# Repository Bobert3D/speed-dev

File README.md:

An ultra fast speed run made Dev board!

Oki so this is a Speedrun dev board so the readme is also going to be Speedrun!
I started with the not so hard schematic!  Schematic!!!

I then continued to the PCB and the layout part so I know where I want things (roughly lol) once I finished that I started to route from the RP2040 outward and then realized that if I wanted this to be ultra compact and cute I needed 4 layers soooo. I did that lol and I continued to do it and then I'm here writing this readme and about to do BOM! Thanks!  PCB Photo!!! 
 3D Render!
If you want to see the CAD/3D design take a peek here!! https://cad.onshape.com/documents/b9c1c579f6d2acbbd7cd123c/w/911443ecb6c1df3a912c9fca/e/5be0e992ba93a5b27c93457b?renderMode=0&uiState=6ac969cc2a2592bfad12f0f4

 BOM!

#BOM!
| Id | Designator                              | Footprint                           | Quantity | Designation                 | Supplier and ref |   |   |
|----|-----------------------------------------|-------------------------------------|----------|-----------------------------|------------------|---|---|
| 1  | SW1                                     | SW_Push_SPST_NO_Alps_SKRK           | 1        | SW_Push                     |                  |   |   |
| 2  | C8,C17                                  | C_0402_1005Metric                   | 2        | 1uF                         |                  |   |   |
| 3  | C11,C15,C7,C16,C13,C12,C9,C10,C5,C14,C6 | C_0402_1005Metric                   | 11       | 0.1uF                       |                  |   |   |
| 4  | Y1                                      | Crystal_SMD_3225-4Pin_3.2x2.5mm     | 1        | 12 MHz                      |                  |   |   |
| 5  | U4                                      | SOT-23                              | 1        | MCP1700x-330xxTT            |                  |   |   |
| 6  | R2,R5,R1,R6                             | R_0402_1005Metric                   | 4        | 5.1K                        |                  |   |   |
| 7  | J3                                      | PinHeader_1x03_P2.54mm_Vertical     | 1        | Conn_01x03                  |                  |   |   |
| 8  | R4                                      | R_0402_1005Metric                   | 1        | 10K                         |                  |   |   |
| 9  | U3                                      | QFN-56-1EP_7x7mm_P0.4mm_EP3.2x3.2mm | 1        | RP2040                      |                  |   |   |
| 10 | C2,C1                                   | C_0201_0603Metric                   | 2        | 10uF                        |                  |   |   |
| 11 | J2,J4                                   | PinHeader_1x20_P2.54mm_Vertical     | 2        | Conn_01x20                  |                  |   |   |
| 12 | R3                                      | R_0402_1005Metric                   | 1        | 1K                          |                  |   |   |
| 13 | U2                                      | SOIC-8_5.3x5.3mm_P1.27mm            | 1        | W25Q128JVS                  |                  |   |   |
| 14 | J1                                      | USB_C_Receptacle_HRO_TYPE-C-31-M-12 | 1        | USB_C_Receptacle_USB2.0_14P |                  |   |   |
| 15 | C4,C3                                   | C_0603_1608Metric                   | 2        | 15pF                        |                  |   |   |

## FAQ

#### BOM?

There are 2 BOM technically one has the LCSC part numbers and the others is a quote from LCSC with links to parts too!

#### Is this good for beginners?

Yes!!! ITS THE BENCHY PCB EQUIVALENT!!

#### How many layers is the PCB?

This is a 4 layer PCB!

#### Can I contribute?

YES YOU CAN!!!! Take a peek at the Contributing section for a better guide on contributing!

## Authors

- [@bobert3d](https://www.github.com/Bobert3D)

- [@vms-hc](https://www.github.com/VMS-HC)

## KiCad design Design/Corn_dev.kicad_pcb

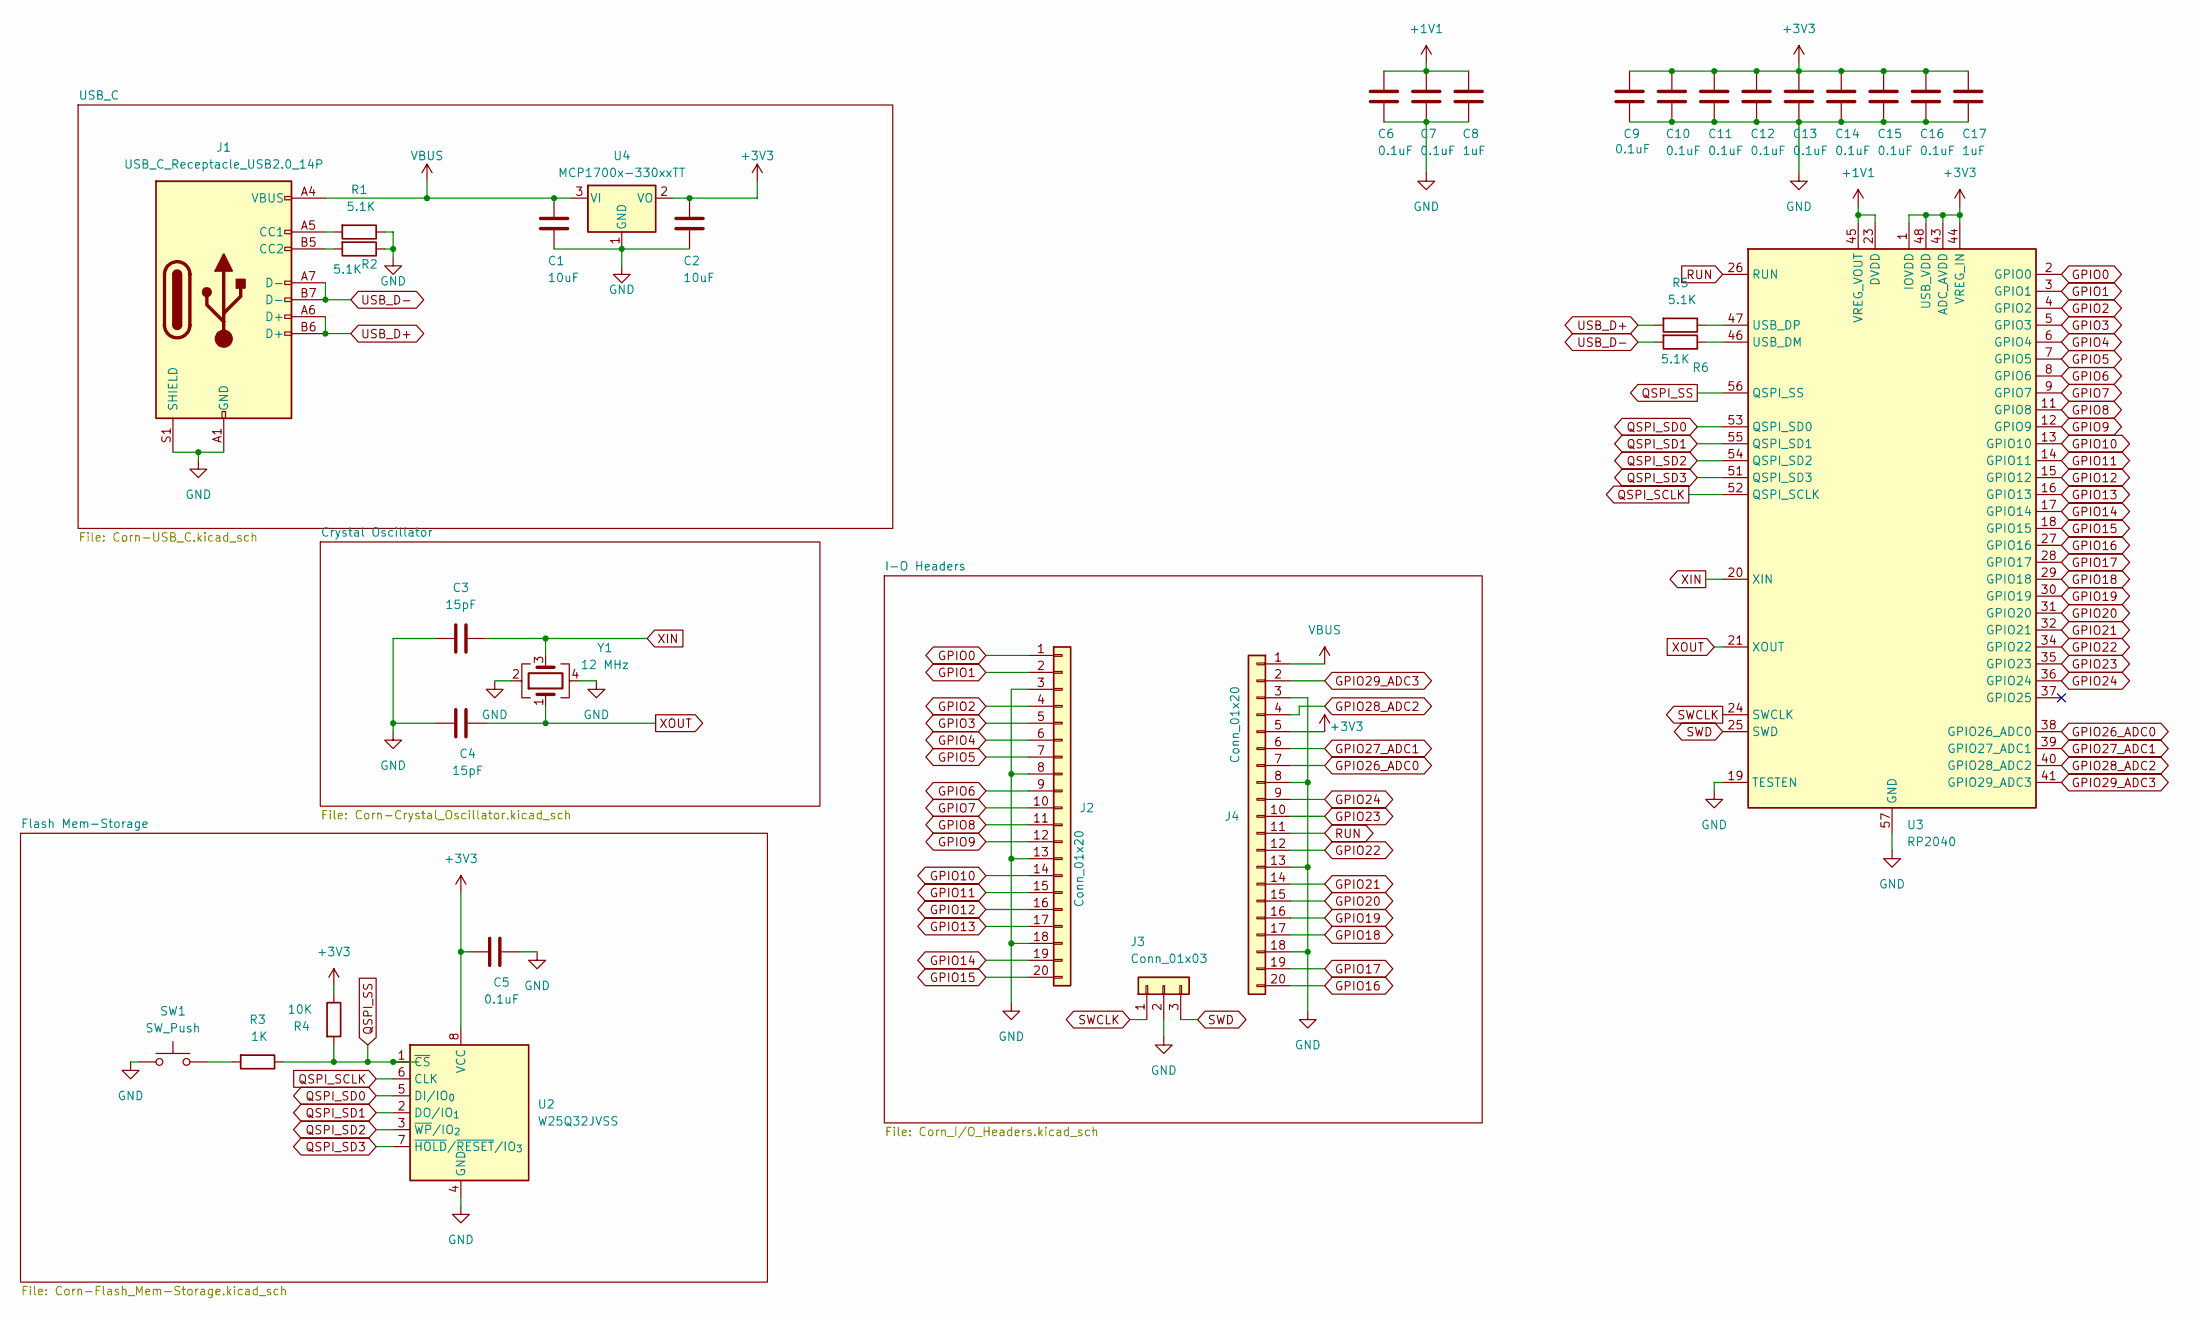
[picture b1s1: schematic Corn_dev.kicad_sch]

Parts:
C1, C2: 10uF; C_0201_0603Metric
C3, C4: 15pF; C_0603_1608Metric
C5, C6, C7, C9, C10, C11, C12, C13, C14, C15, C16: 0.1uF; C_0402_1005Metric
C8, C17: 1uF; C_0402_1005Metric
J1: USB_C_Receptacle_USB2.0_14P; USB_C_Receptacle_HRO_TYPE-C-31-M-12
J2, J4: Conn_01x20; PinHeader_1x20_P2.54mm_Vertical
J3: Conn_01x03; PinHeader_1x03_P2.54mm_Vertical
R1, R2, R5, R6: 5.1K; R_0402_1005Metric
R3: 1K; R_0402_1005Metric
R4: 10K; R_0402_1005Metric
SW1: SW_Push; SW_Push_SPST_NO_Alps_SKRK
U2: W25Q32JVSS; SOIC-8_5.3x5.3mm_P1.27mm
U3: RP2040; QFN-56-1EP_7x7mm_P0.4mm_EP3.2x3.2mm
U4: MCP1700x-330xxTT; SOT-23
Y1: 12 MHz; Crystal_SMD_3225-4Pin_3.2x2.5mm

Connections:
+1V1: C6.1, C7.1, C8.1, U3.23 (DVDD), U3.45 (VREG_VOUT), U3.50 (DVDD)
+3V3: C2.1, C5.1, C9.1, C10.1, C11.1, C12.1, C13.1, C14.1, C15.1, C16.1, C17.1, J4.5, R4.1, U2.8 (VCC), U3.1 (IOVDD), U3.10 (IOVDD), U3.22 (IOVDD), U3.33 (IOVDD), U3.42 (IOVDD), U3.43 (ADC_AVDD), U3.44 (VREG_IN), U3.48 (USB_VDD), U3.49 (IOVDD), U4.2 (VO)
GND: C1.2, C2.2, C3.1, C4.1, C5.2, C6.2, C7.2, C8.2, C9.2, C10.2, C11.2, C12.2, C13.2, C14.2, C15.2, C16.2, C17.2, J1.A1 (GND), J1.A12 (GND), J1.B1 (GND), J1.B12 (GND), J1.S1 (SHIELD), J2.3, J2.8, J2.13, J2.18, J3.2, J4.3, J4.8, J4.13, J4.18, R1.1, R2.1, SW1.1, U2.4 (GND), U3.19 (TESTEN), U3.57 (GND), U4.1 (GND), Y1.2, Y1.4
GPIO0: J2.1, U3.2 (GPIO0)
GPIO1: J2.2, U3.3 (GPIO1)
GPIO2: J2.4, U3.4 (GPIO2)
GPIO3: J2.5, U3.5 (GPIO3)
GPIO4: J2.6, U3.6 (GPIO4)
GPIO5: J2.7, U3.7 (GPIO5)
GPIO6: J2.9, U3.8 (GPIO6)
GPIO7: J2.10, U3.9 (GPIO7)
GPIO8: J2.11, U3.11 (GPIO8)
GPIO9: J2.12, U3.12 (GPIO9)
GPIO10: J2.14, U3.13 (GPIO10)
GPIO11: J2.15, U3.14 (GPIO11)
GPIO12: J2.16, U3.15 (GPIO12)
GPIO13: J2.17, U3.16 (GPIO13)
GPIO14: J2.19, U3.17 (GPIO14)
GPIO15: J2.20, U3.18 (GPIO15)
GPIO16: J4.20, U3.27 (GPIO16)
GPIO17: J4.19, U3.28 (GPIO17)
GPIO18: J4.17, U3.29 (GPIO18)
GPIO19: J4.16, U3.30 (GPIO19)
GPIO20: J4.15, U3.31 (GPIO20)
GPIO21: J4.14, U3.32 (GPIO21)
GPIO22: J4.12, U3.34 (GPIO22)
GPIO23: J4.10, U3.35 (GPIO23)
GPIO24: J4.9, U3.36 (GPIO24)
GPIO26_ADC0: J4.7, U3.38 (GPIO26_ADC0)
GPIO27_ADC1: J4.6, U3.39 (GPIO27_ADC1)
GPIO28_ADC2: J4.4, U3.40 (GPIO28_ADC2)
GPIO29_ADC3: J4.2, U3.41 (GPIO29_ADC3)
unnamed: J1.A5 (CC1), R1.2
unnamed: J1.B5 (CC2), R2.2
unnamed: R3.2, SW1.2
unnamed: R6.1, U3.46 (USB_DM)
unnamed: R5.1, U3.47 (USB_DP)
QSPI_SCLK: U2.6 (CLK), U3.52 (QSPI_SCLK)
QSPI_SD0: U2.5 (DI/IO_{0}), U3.53 (QSPI_SD0)
QSPI_SD1: U2.2 (DO/IO_{1}), U3.55 (QSPI_SD1)
QSPI_SD2: U2.3 (~WP/IO_{2}), U3.54 (QSPI_SD2)
QSPI_SD3: U2.7 (~HOLD/~RESET/IO_{3}), U3.51 (QSPI_SD3)
QSPI_SS: R3.1, R4.2, U2.1 (~CS), U3.56 (QSPI_SS)
RUN: J4.11, U3.26 (RUN)
SWCLK: J3.1, U3.24 (SWCLK)
SWD: J3.3, U3.25 (SWD)
USB_D+: J1.A6 (D+), J1.B6 (D+), R5.2
USB_D-: J1.A7 (D-), J1.B7 (D-), R6.2
VBUS: C1.1, J1.A4 (VBUS), J1.A9 (VBUS), J1.B4 (VBUS), J1.B9 (VBUS), J4.1, U4.3 (VI)
XIN: C3.2, U3.20 (XIN), Y1.3
XOUT: C4.2, U3.21 (XOUT), Y1.1

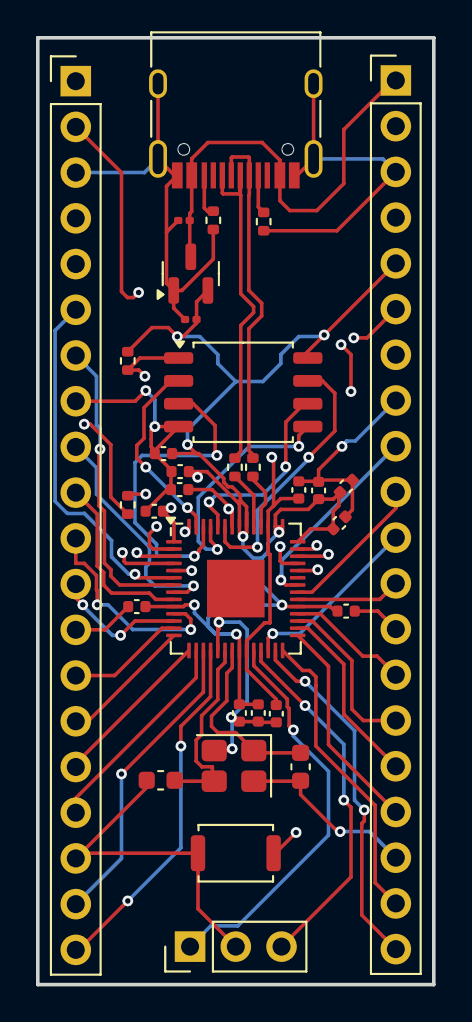
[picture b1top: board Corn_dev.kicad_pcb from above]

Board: 4 copper layers, 22.0 x 52.6 mm, 32 parts (0 on the bottom side), 51 nets.

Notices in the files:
README.md:
MIT License
